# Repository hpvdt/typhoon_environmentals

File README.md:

# Typhoon Environmentals

General template repository for our hardware projects, especially one-off and self-contained projects like custom test equipment. This template assumes that the hardware is being designed in KiCad.

## Organization

Pretty self-explanitory, put hardware related files into the `hardware` folder, firmware in the `firmware` folder. Other folders can be added as needed: for example a `media` folder is handy for storing pictures related to a project which can be used in documentation.

## Conventions

Partly for consistency, partly for functionality; please follow the following conventions:

- Try to keep folder names to single words and all lowercase
- Use underscores to separate words in names (e.g. `board_rev1`). **DO NOT USE SPACES! ESPECIALLY FOR FOLDERS CONTAINING CODE!** Spaces in file paths may cause issues in compilers and such so best to avoid them entirely.

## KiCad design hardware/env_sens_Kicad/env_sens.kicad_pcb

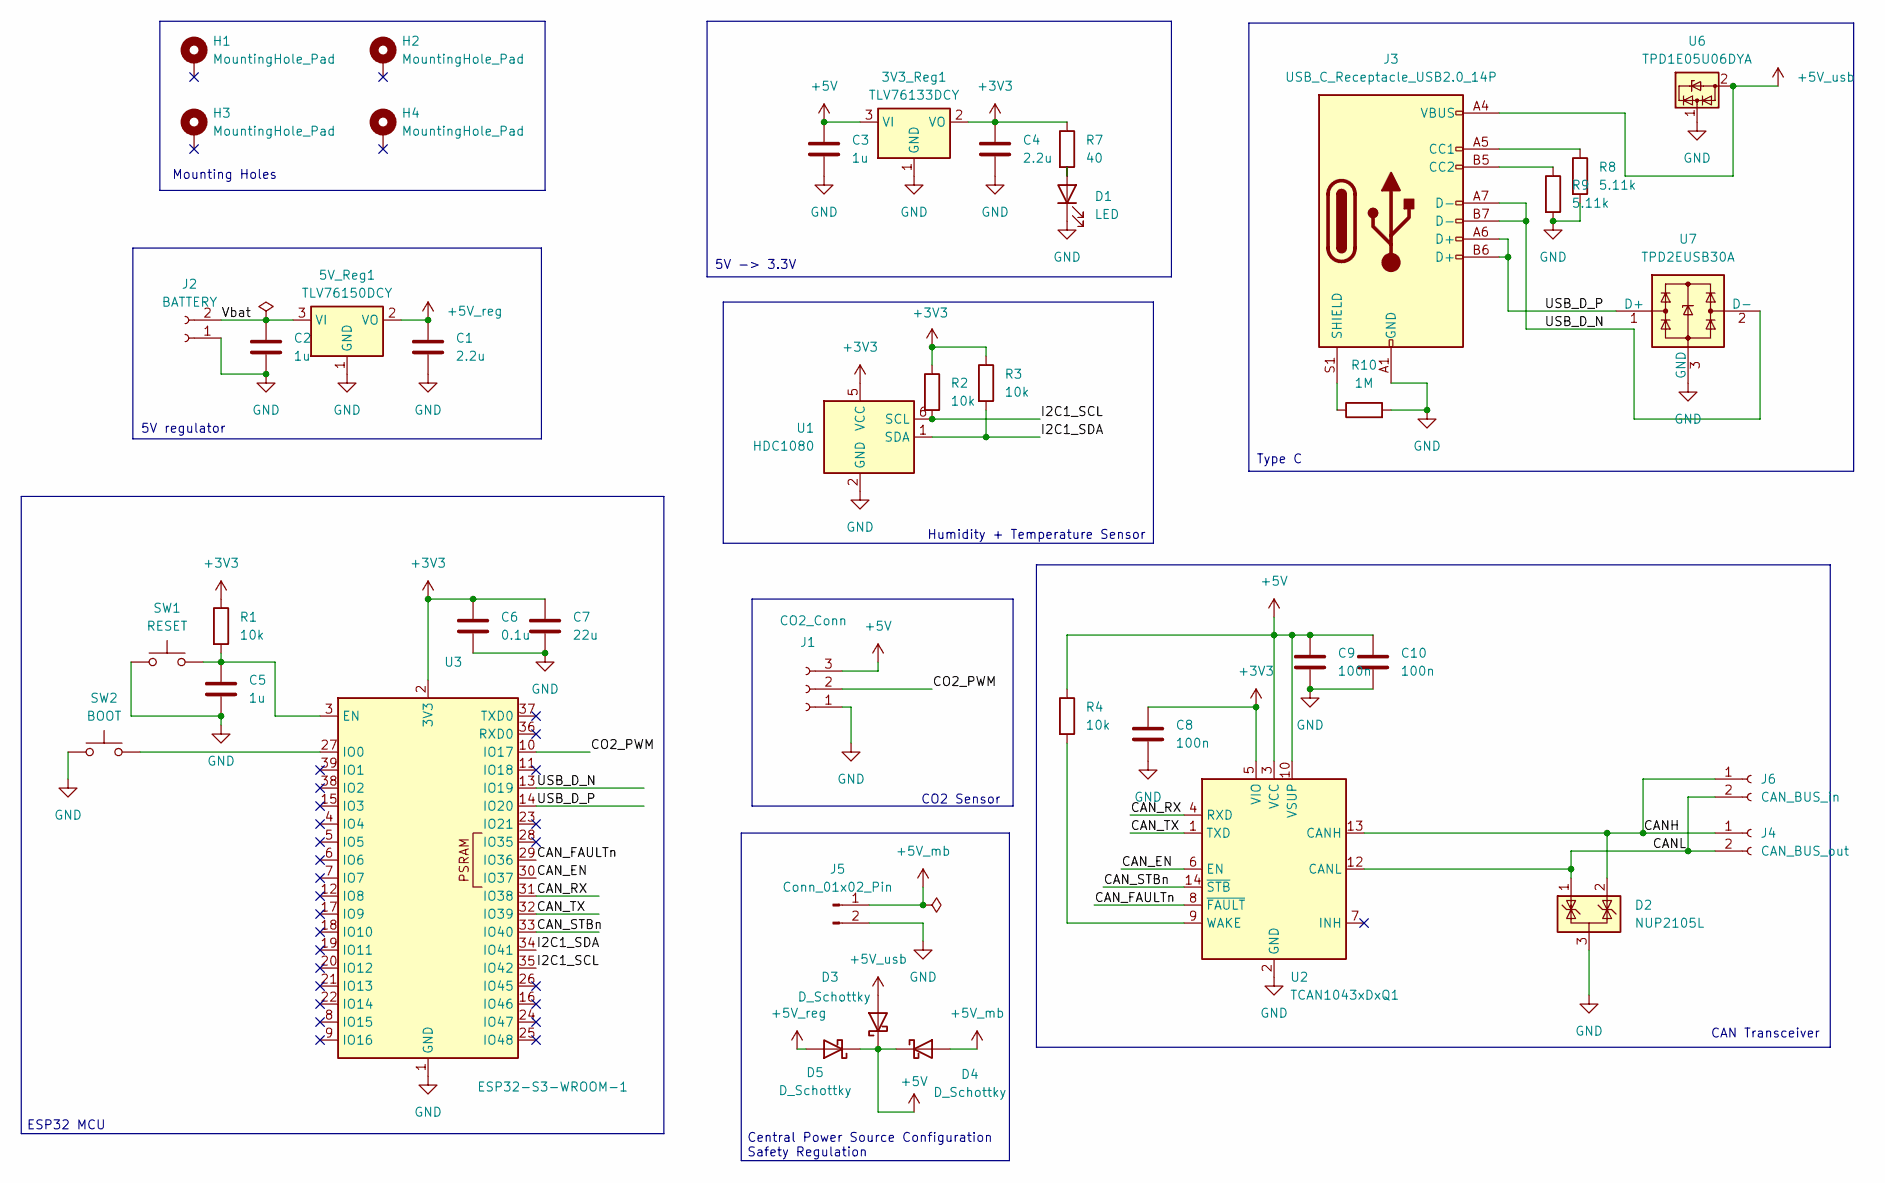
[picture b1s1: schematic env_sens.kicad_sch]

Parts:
3V3_Reg1: TLV76133DCY; SOT-223-3_TabPin2
5V_Reg1: TLV76150DCY; SOT-223-3_TabPin2
C1, C4: 2.2u; C_0805_2012Metric_Pad1.18x1.45mm_HandSolder
C2, C3, C5: 1u; C_0805_2012Metric_Pad1.18x1.45mm_HandSolder
C6: 0.1u; C_0805_2012Metric_Pad1.18x1.45mm_HandSolder
C7: 22u; C_0805_2012Metric_Pad1.18x1.45mm_HandSolder
C8, C9, C10: 100n; C_0805_2012Metric_Pad1.18x1.45mm_HandSolder
D1: LED; LED_0805_2012Metric_Pad1.15x1.40mm_HandSolder
D2: NUP2105L; SOT-23
D3, D4, D5: D_Schottky; D_SOD-123
H1, H2, H3, H4: MountingHole_Pad; MountingHole_2.7mm_M2.5
J1: CO2_Conn; JST_XH_S3B-XH-A_1x03_P2.50mm_Horizontal
J2: BATTERY; AMASS_XT30PW-M_1x02_P2.50mm_Horizontal
J3: USB_C_Receptacle_USB2.0_14P; USB_C_Receptacle_Amphenol_12401610E4-2A
J4: CAN_BUS_out; JST_EH_S2B-EH_1x02_P2.50mm_Horizontal
J5: Conn_01x02_Pin; JST_EH_S2B-EH_1x02_P2.50mm_Horizontal
J6: CAN_BUS_in; JST_EH_S2B-EH_1x02_P2.50mm_Horizontal
R1, R2, R3, R4: 10k; R_0805_2012Metric_Pad1.20x1.40mm_HandSolder
R7: 40; R_0805_2012Metric_Pad1.20x1.40mm_HandSolder
R8, R9: 5.11k; R_0805_2012Metric_Pad1.20x1.40mm_HandSolder
R10: 1M; R_0805_2012Metric_Pad1.20x1.40mm_HandSolder
SW1: RESET; SW_PUSH_6mm
SW2: BOOT; SW_PUSH_6mm
U1: HDC1080; Texas_PWSON-N6
U2: TCAN1043xDxQ1; SOIC-14_3.9x8.7mm_P1.27mm
U3: ESP32-S3-WROOM-1
U6: TPD1E05U06DYA; D_SOD-523
U7: TPD2EUSB30A; Texas_DRT-3

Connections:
+3V3: 3V3_Reg1.2 (VO), C4.1, C6.1, C7.1, C8.1, R1.1, R2.1, R3.1, R7.1, U1.5 (VCC), U2.5 (VIO), U3.2 (3V3)
+5V: 3V3_Reg1.3 (VI), C3.1, C9.1, C10.1, D3.1 (K), D4.1 (K), D5.1 (K), J1.3, R4.1, U2.3 (VCC), U2.10 (VSUP)
+5V_mb: D4.2 (A), J5.1
+5V_reg: 5V_Reg1.2 (VO), C1.1, D5.2 (A)
+5V_usb: D3.2 (A), J3.A4 (VBUS), J3.A9 (VBUS), J3.B4 (VBUS), J3.B9 (VBUS), U6.2 (GND)
/CANH: D2.2 (K), J4.1, J6.1, U2.13 (CANH)
/CANL: D2.1 (K), J4.2, J6.2, U2.12 (CANL)
/CAN_EN: U2.6 (EN), U3.30 (IO37)
/CAN_FAULTn: U2.8 (~FAULT), U3.29 (IO36)
/CAN_RX: U2.4 (RXD), U3.31 (IO38)
/CAN_STBn: U2.14 (~STB), U3.33 (IO40)
/CAN_TX: U2.1 (TXD), U3.32 (IO39)
/CO2_PWM: J1.2, U3.10 (IO17)
/I2C1_SCL: R2.2, U1.6 (SCL), U3.35 (IO42)
/I2C1_SDA: R3.2, U1.1 (SDA), U3.34 (IO41)
/USB_D_N: J3.A7 (D-), J3.B7 (D-), U3.13 (IO19), U7.2 (D-)
/USB_D_P: J3.A6 (D+), J3.B6 (D+), U3.14 (IO20), U7.1 (D+)
/Vbat: 5V_Reg1.3 (VI), C2.1, J2.2
GND: 3V3_Reg1.1 (GND), 5V_Reg1.1 (GND), C1.2, C2.2, C3.2, C4.2, C5.2, C6.2, C7.2, C8.2, C9.2, C10.2, D1.1 (K), D2.3 (A), J1.1, J2.1, J3.A1 (GND), J3.A12 (GND), J3.B1 (GND), J3.B12 (GND), J5.2, R8.2, R9.2, R10.2, SW1.1, SW2.1, U1.2 (GND), U2.2 (GND), U3.1 (GND), U3.40 (GND), U3.41 (GND), U6.1 (I/O), U7.3 (GND)
unnamed: D1.2 (A), R7.2
unnamed: J3.A5 (CC1), R8.1
unnamed: J3.B5 (CC2), R9.1
unnamed: J3.S1 (SHIELD), R10.1
unnamed: R4.2, U2.9 (WAKE)
unnamed: C5.1, R1.2, SW1.2, U3.3 (EN)
unnamed: SW2.2, U3.27 (IO0)

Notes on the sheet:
Mounting Holes
ESP32 MCU
Type C
CAN Transceiver
Humidity + Temperature Sensor
5V -> 3.3V
CO2 Sensor
5V regulator
Central Power Source Configuration Safety Regulation

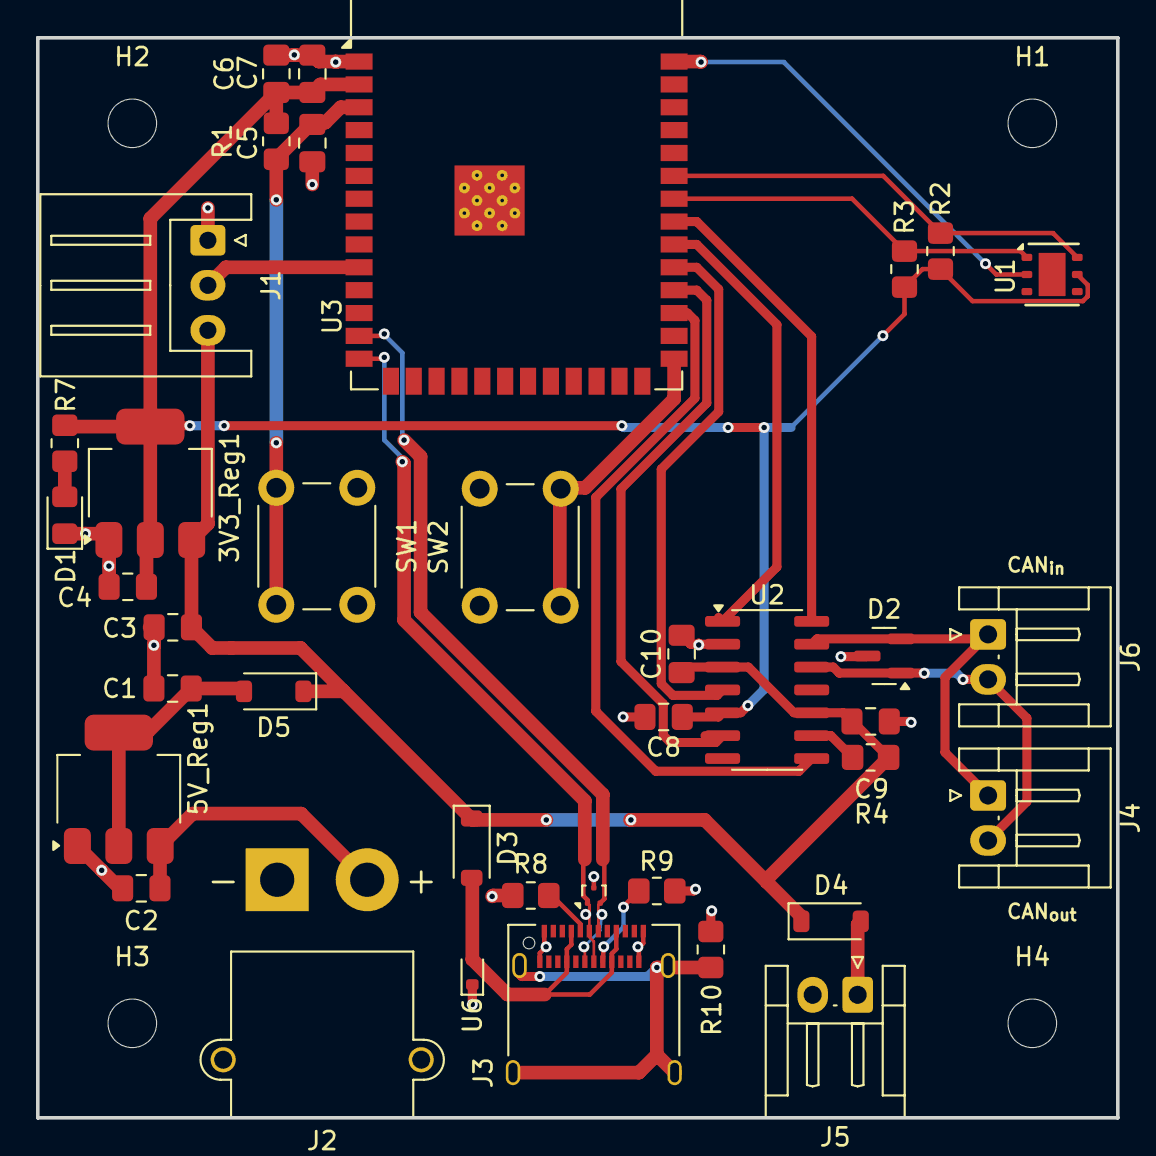
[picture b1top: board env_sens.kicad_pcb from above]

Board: 2 copper layers, 60.0 x 60.0 mm, 42 parts (0 on the bottom side), 26 nets.

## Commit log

2024-07-12 copied files from the original typhoon electronics repo into here
2024-10-05 Uploaded files from typhoon electronics
2024-10-14 Added the central power source configuration and added some comments
2024-10-14 Added central power source configuration from mother board
    Central power source configuration from mother board + safety regulation
2024-10-19 Changed MB input voltage to 5V
2024-11-04 Updated layout with schematic changes
2024-11-17 Replaced with schottkey dioides & did production files
